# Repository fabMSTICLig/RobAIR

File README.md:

<br />Les différentes partie de ce projet sont mise à disposition selon les termes de la <a rel="license" href="http://creativecommons.org/licenses/by-nc-sa/3.0/fr/">Licence Creative Commons Attribution - Pas d’Utilisation Commerciale - Partage dans les Mêmes Conditions 3.0 France</a>.

---

Avec le soutien financier de 

---

# RobAIR

## Installation

### Pré-requis

- Ubuntu 20.04 LTS
- Git

- L'utilisateur courant doit avoir les droits root via `sudo`

### Procédure

- Téléchargez le dépôt
```bash
git clone https://github.com/FabmsticLig/RobAIR.git
```
- Lancez le script d'installation
```bash
cd RobAIR
./scripts/install.bash
```
- Si l'utilisateur courant n'était préalablement pas dans le groupe `dialout`
(autrement dit, si le script d'installation a affiché "donne à l'utilisateur
l'accès aux ports série"), redémarrez votre session
- Avec la carte Arduino branchée, lancez le chargement des programmes
```bash
robair reload
```

Le script d'installation récupérera des dépôts les paquets nécessaires et
effectuera la configuration initiale de RobAIR. Quelques variables seront aussi
ajoutées au bashrc de l'utilisateur, en plus d'un service systemd permettant de
démarrer et arrêter les programmes.

## Utilisation

### Procédure

Sur RobAIR
- Allumez le robot
- Allumez la tablette
- Branchez la tablette
- Connectez vous au réseau wifi. Si votre RobAIR dispose d'une carte wifi
externe pensez à déconnecter la carte wifi interne (INTEL).
- Ouvrez un terminal et lancez la commande `robair ip`, notez l'adresse IP indiquée (ROBAIR_IP)
- Lancez la commande `robair start`
- Ouvrez chromium et allez à l'adresse https://ROBAIR_IP:6080 (en remplaçant
ROBAIR_IP par l'adresse notée précédemment)

Sur la machine utilisateur
- Allez à l'adresse http://ROBAIR_IP:6081
- Récupérez l'autorité de certification et installez-la sur le navigateur client
- Allez à l'adresse https://ROBAIR_IP:6080

### Gestion

La partie logicielle de RobAIR peut être contrôlée depuis la tablette via le
programme `robair`. Utilisez les commandes suivantes pour respectivement lancer,
arrêter ou redémarrer le logiciel.
```bash
robair start
robair stop
robair restart
```

Si `systemd` est installé (par défaut sous Ubuntu), ces commandes pilotent
RobAIR via un service systemd en session utilisateur. L'intérêt est
essentiellement de permettre le lancement de RobAIR au démarrage, puis de gérer
automatiquement les erreurs (`systemd` relancera le logiciel s'il venait à
planter). Avec quelques modifications il serait aussi possible de
configurer l'activation par socket.

Le programme `robair` permet aussi la mise à jour du logiciel via cette commande
```bash
$ robair update
```
Cela récupérera la dernière version de RobAIR via Git, recompilera les
programmes et mettra à jour la carte Arduino.

## Développement

RobAIR est développé au-dessus de l'architecture [ROS][1].

L'essentiel du code du robot se trouve dans `arduino/libraries`, avec le point
d'entrée dans `arduino/robairarduino`.

L'interface est servie par un serveur `nodejs` résidant dans `interface`.

Si vous souhaitez tester des modifications locales, vous pouvez recompiler les
programmes et recharger la carte Arduino via cette commande
```bash
robair reload
```

 [1]: http://www.ros.org/

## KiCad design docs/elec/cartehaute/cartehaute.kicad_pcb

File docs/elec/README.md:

#Fichiers mécaniques

Le fichier global.xml s'ouvre avec l'utilitaire umlet ou la version en ligne umletino.

##Kicad

Les schémas électroniques sont conçus avec le logiciel open source Kicad.

| Fichiers/dossiers         | Explication                                             |
|---------------------------|---------------------------------------------------------|
| robair.lib                | librairie kicad des composants du projet                |
| robair.pretty             | librairie d'empreinte kicad des composants du projet    | 
| alim5v                    | le projet de la carte d'alimnetation                    | 
| cartehaute                | le projet de la carte de connexion placé dans le buste  |

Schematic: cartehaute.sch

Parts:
P1: D1; Pin_Header_Straight_1x03_Pitch2.54mm
P2: D2; Pin_Header_Straight_1x03_Pitch2.54mm
P3: D3; Pin_Header_Straight_1x03_Pitch2.54mm
P4: D4; Pin_Header_Straight_1x03_Pitch2.54mm
P5: D5; Pin_Header_Straight_1x03_Pitch2.54mm
P6, P8: CONN_01X02; PhoenixContact_MC-G_02x5.08mm_Angled
P7: CONN_01X05; Pin_Header_Straight_1x05_Pitch2.54mm

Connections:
/5V: P1.2, P2.2, P3.2, P4.2, P5.2, P6.2, P8.2
/GND: P1.1, P2.1, P3.1, P4.1, P5.1, P6.1, P8.1
unnamed: P1.3, P7.1
unnamed: P2.3, P7.2
unnamed: P3.3, P7.3
unnamed: P4.3, P7.4
unnamed: P5.3, P7.5

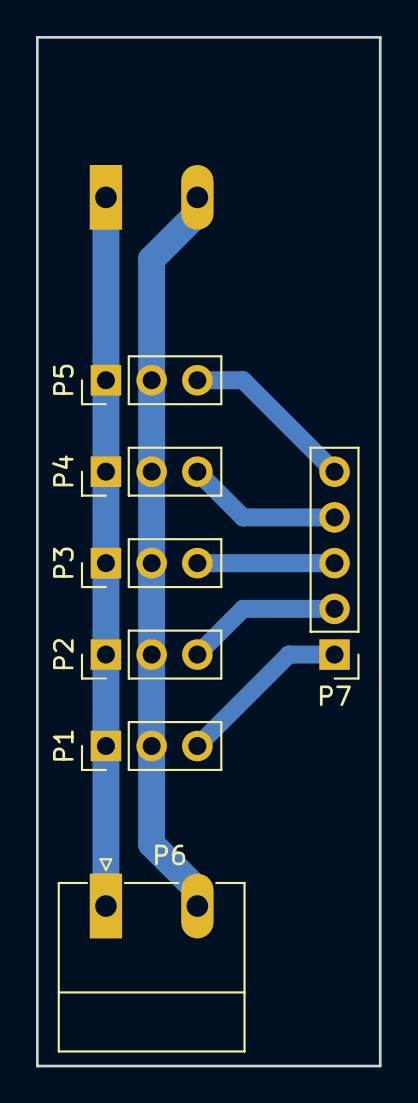
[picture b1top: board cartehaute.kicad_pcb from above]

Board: 2 copper layers, 19.1 x 57.2 mm, 8 parts (1 on the bottom side), 7 nets.

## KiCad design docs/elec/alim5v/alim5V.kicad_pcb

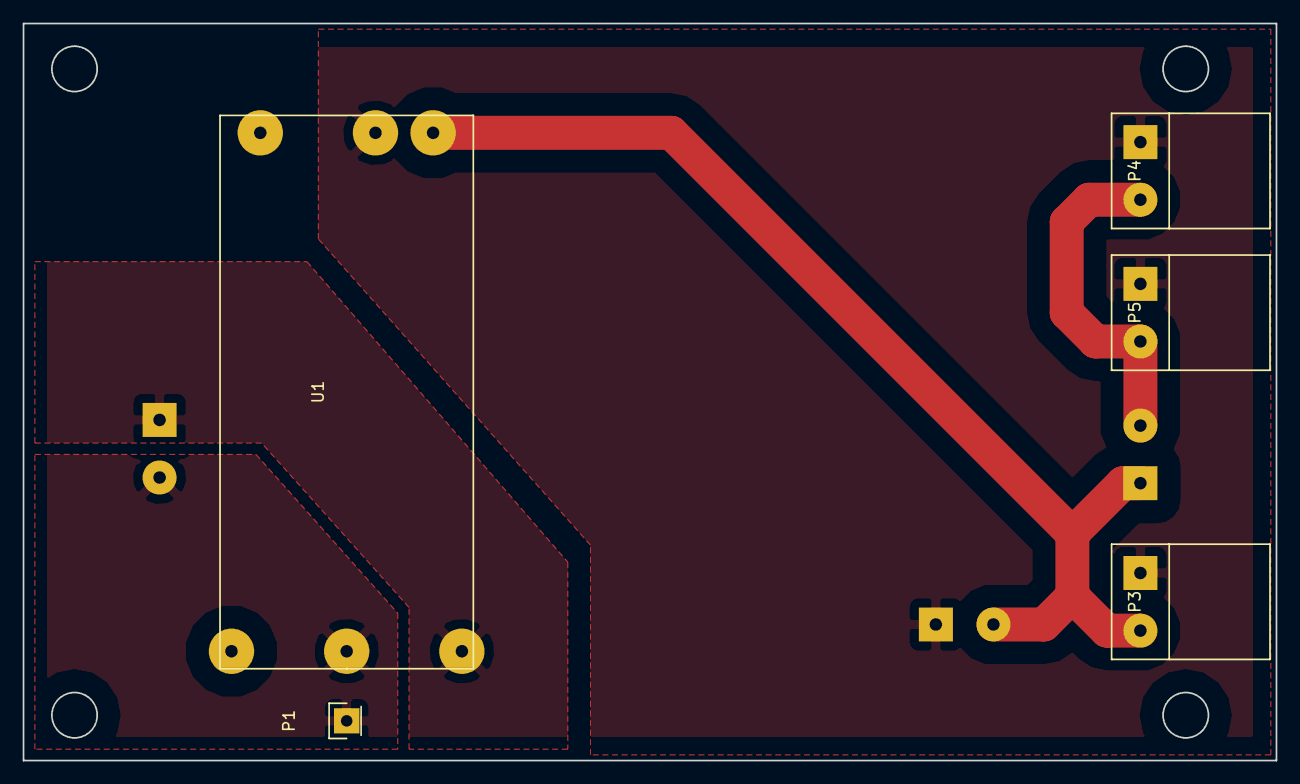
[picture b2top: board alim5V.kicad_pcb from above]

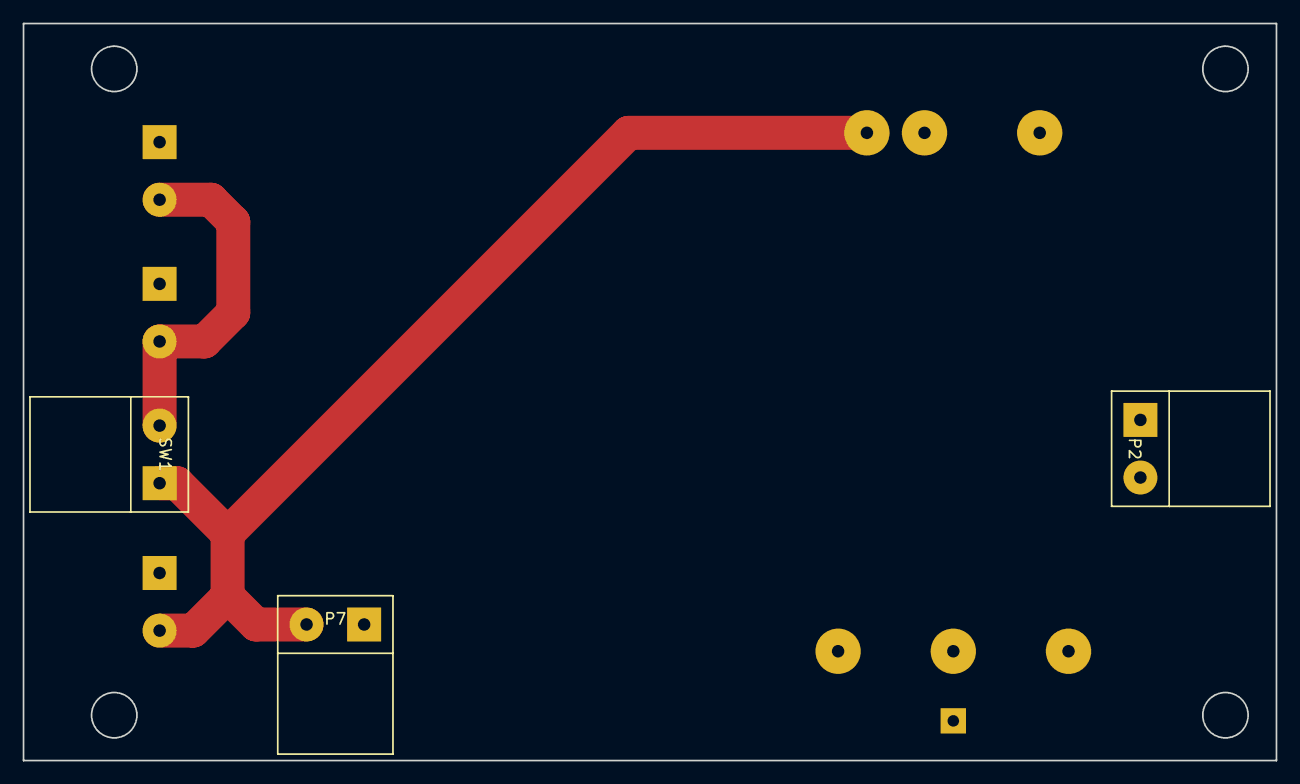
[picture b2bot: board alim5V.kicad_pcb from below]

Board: 2 copper layers, 110.5 x 65.0 mm, 8 parts (3 on the bottom side), 5 nets.

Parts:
P1: GND Ardui; Pin_Header_Straight_1x01
P2: 5V out; Bornier5mm
P3: MD49; Bornier5mm
P4: Charg; Bornier5mm
P5: Batt; Bornier5mm
P7: AUX; Bornier5mm
SW1: SW; Bornier5mm
U1: UEI30-050-Q12P-C

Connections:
/GND5: P1.1, P2.2, U1.5
/GND24: P3.1, P4.1, P5.1, P7.1, U1.2
unnamed: P2.1, U1.4
unnamed: P3.2, P7.2, SW1.1, U1.1
unnamed: P4.2, P5.2, SW1.2

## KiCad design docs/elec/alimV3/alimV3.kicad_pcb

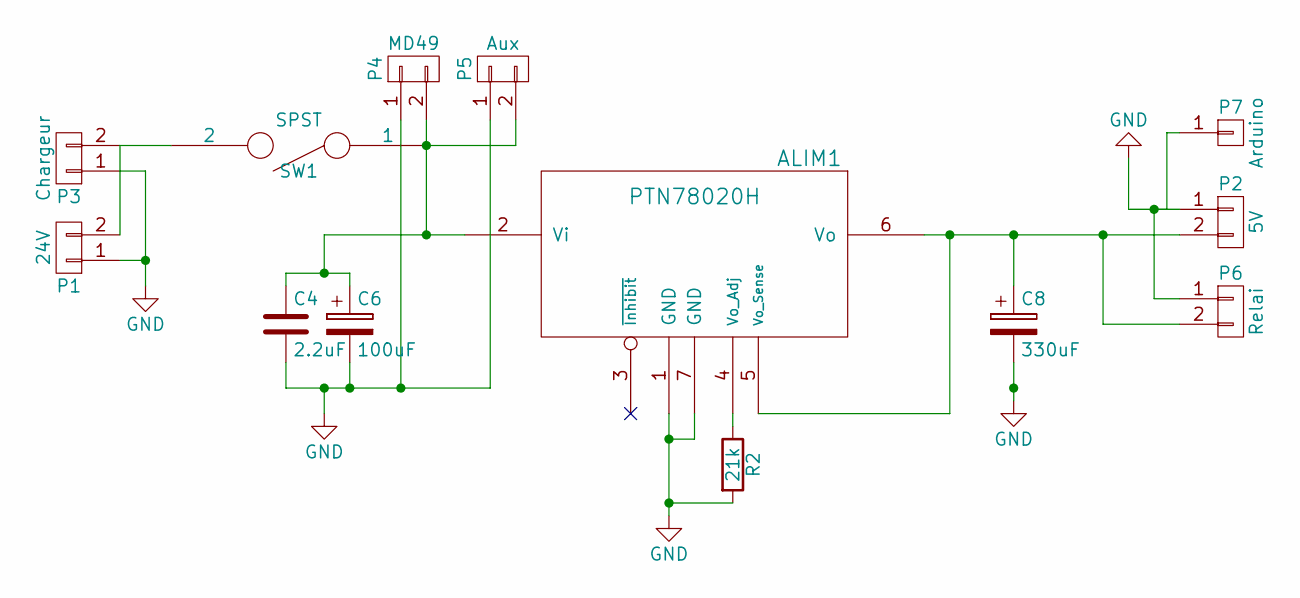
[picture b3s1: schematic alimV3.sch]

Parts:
ALIM1: PTN78020H; PTN78020
C4: 2.2uF; C_1210_HandSoldering
C6: 100uF; CP_Radial_D6.3mm_P2.50mm
C8: 330uF; CP_Radial_D10.0mm_P5.00mm
P1: 24V; Bornier5mm
P2: 5V; Bornier5mm
P3: Chargeur; Bornier5mm
P4: MD49; Bornier5mm
P5: Aux; Bornier5mm
P6: Relai; Socket_Strip_Straight_2x01_Pitch2.54mm
P7: Arduino; Socket_Strip_Straight_1x01_Pitch2.54mm
R2: 21k; R_Axial_DIN0204_L3.6mm_D1.6mm_P2.54mm_Vertical
SW1: SPST; Bornier5mm

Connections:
GND: ALIM1.1 (GND), ALIM1.7 (GND), C4.2, C6.2, C8.2, P1.1, P2.1, P3.1, P4.1, P5.1, P6.1, P7.1, R2.2; also elsewhere on the board
unnamed 1: ALIM1.2 (Vi), C4.1, C6.1, P4.2, P5.2, SW1.1; also elsewhere on the board
unnamed 3: ALIM1.4 (Vo_Adj), R2.1; also elsewhere on the board
unnamed 4: ALIM1.5 (Vo_Sense), ALIM1.6 (Vo), C8.1, P2.2, P6.2; also elsewhere on the board
unnamed: P1.2, P3.2, SW1.2

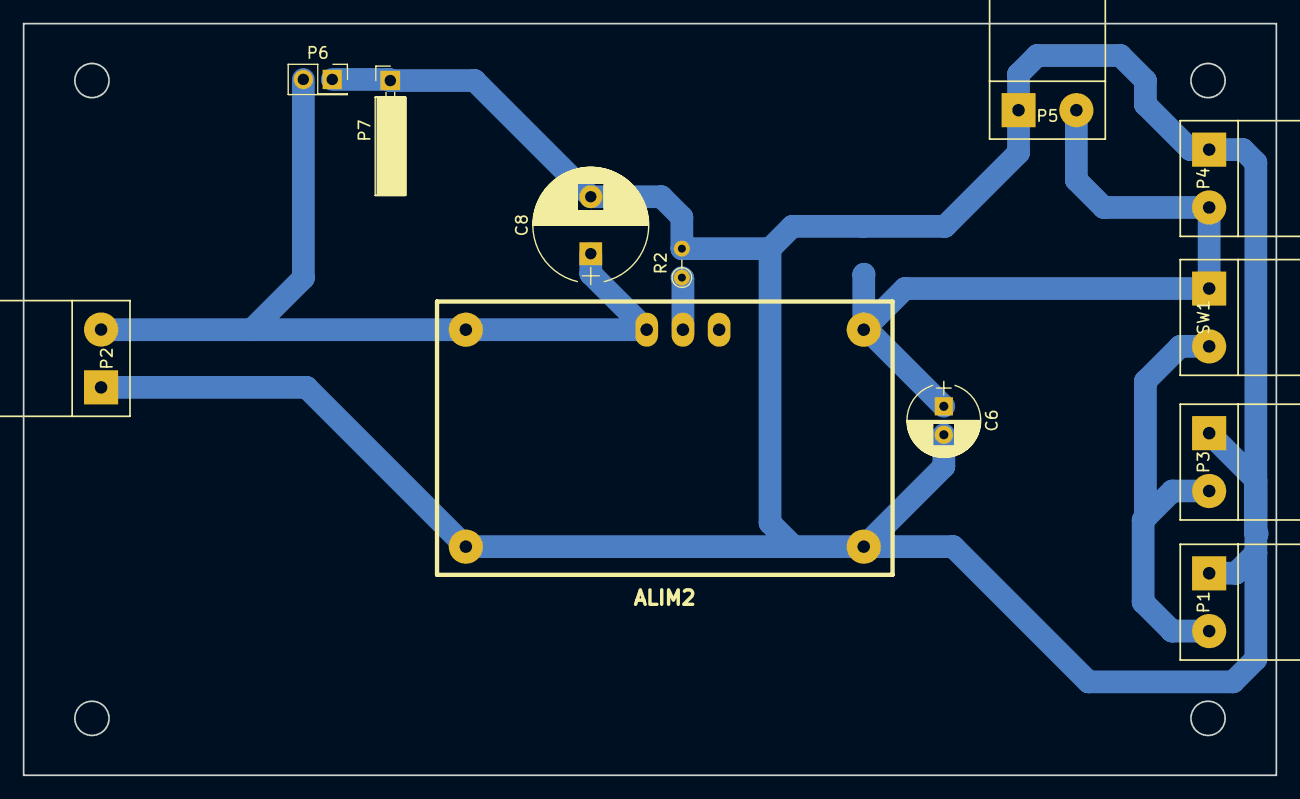
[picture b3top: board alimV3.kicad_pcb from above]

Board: 2 copper layers, 110.0 x 66.0 mm, 13 parts (1 on the bottom side), 5 nets.

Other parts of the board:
ALIM2: PTN78020H; PTN78020

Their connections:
GND: ALIM2.1, ALIM2.7; also elsewhere on the board
unnamed 1: ALIM2.2; also elsewhere on the board
unnamed 3: ALIM2.4; also elsewhere on the board
unnamed 4: ALIM2.5, ALIM2.6; also elsewhere on the board

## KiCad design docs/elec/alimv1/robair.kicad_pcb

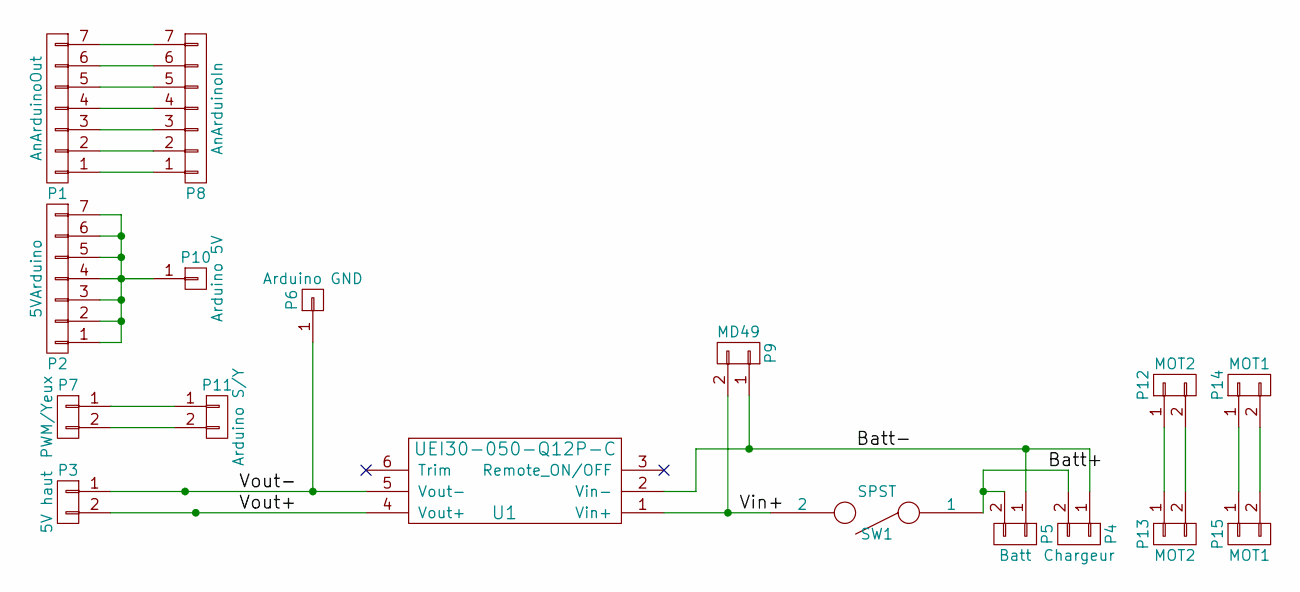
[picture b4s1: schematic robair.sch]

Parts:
P1: AnArduinoOut; Pin_Header_Straight_1x07
P2: 5VArduino; Pin_Header_Straight_1x07
P3: 5V haut; Bornier5mm
P4: Chargeur; Bornier5mm
P5: Batt; Bornier5mm
P6: Arduino GND; Pin_Header_Straight_1x01
P7: PWM/Yeux; Pin_Header_Straight_1x02
P8: AnArduinoIn; Pin_Header_Straight_1x07
P9: MD49; Bornier5mm
P10: Arduino 5V; Pin_Header_Straight_1x01
P11: Arduino S/Y; Pin_Header_Straight_1x02
P12: MOT2; BornierMoteur
P13: MOT2; Bornier5mm
P14: MOT1; BornierMoteur
P15: MOT1; Bornier5mm
SW1: SPST; Bornier5mm
U1: UEI30-050-Q12P-C

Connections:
/Batt+: P4.2, P5.2, SW1.1
/Batt-: P4.1, P5.1, P9.1, U1.2 (Vin-)
/Vin+: P9.2, SW1.2, U1.1 (Vin+)
/Vout+: P3.2, U1.4 (Vout+)
/Vout-: P3.1, P6.1, U1.5 (Vout-)
unnamed: P1.1, P8.1
unnamed: P1.2, P8.2
unnamed: P1.3, P8.3
unnamed: P1.4, P8.4
unnamed: P1.5, P8.5
unnamed: P1.6, P8.6
unnamed: P1.7, P8.7
unnamed: P2.1, P2.2, P2.3, P2.4, P2.5, P2.6, P2.7, P10.1
unnamed: P7.1, P11.1
unnamed: P7.2, P11.2
unnamed: P12.1, P13.1
unnamed: P12.2, P13.2
unnamed: P14.1, P15.1
unnamed: P14.2, P15.2

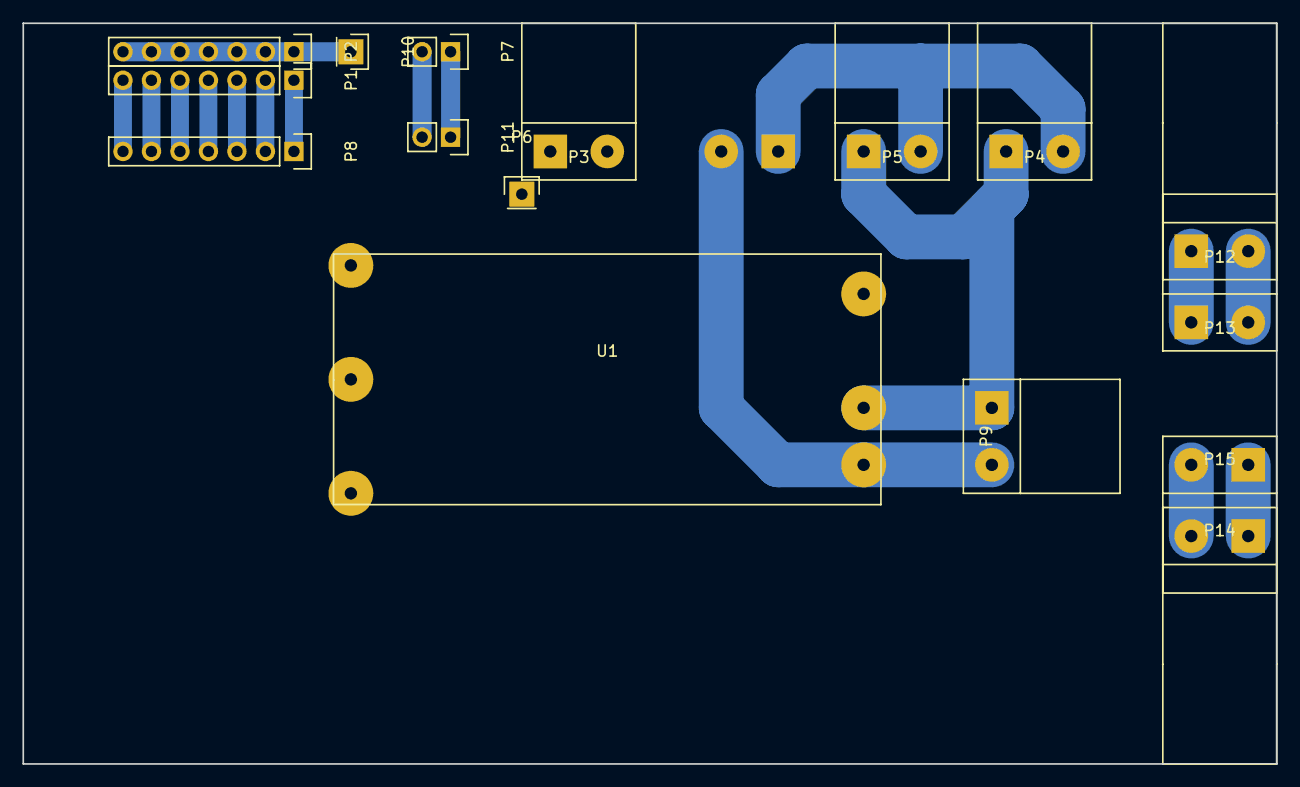
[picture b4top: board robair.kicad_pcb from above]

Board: 2 copper layers, 111.8 x 66.0 mm, 17 parts (1 on the bottom side), 19 nets.

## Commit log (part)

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2016-09-20 création des scripts d'installasion
2016-09-20 Update README.md
    Inline bash style
2016-09-23 correction install.sh
2016-09-26 correction install derrière proxy
2016-10-07 interface glyphicons fonts et jqerry libs
2016-10-07 ajout projet arduino et librairies
2016-10-17 interface jquery
2016-10-18 changement de ports et avancer webinterface
2016-10-20 ajout dossier doc
2016-10-21 fix bug st
2016-10-26 ajout des yeux et rotation tête
2016-10-28 kicad project
2016-11-06 Corrige le bug du proxy https dans install.bash
2016-11-12 fix install.bash
    option -e enlevée, l'option non compatible avec `cat ~/.bashrc | grep ROBAIR`, supposément l'utilisation des ``
2016-11-12 ajout pont scratch
2016-11-20 elec : alim haut, alim bas. mecas
2016-11-24 ros ajout de rosparam dans ros arduino, gestion des bumper (en cours), gestion de l'aru
2016-11-27 correction de la résoltion de ROBAIR_IP en cas de connection offline
2016-11-27 ajout du touché
2016-11-28 ajout script de démarage correction de la gestion des yeux bumper ok touch ok
2016-11-28 ajout des params touchXTresh
2016-11-29 changement param touch
2016-11-29 changement system start & stop & restart
2016-11-29 gestion de la fermeture de la fenetre de controle
2016-12-01 netoyage des fichiers meca, création de la base de charge
2016-12-06 meca ajout support cartes
2016-12-06 ajout carte alim 5V
2016-12-08 Ajout de l'option pour mettre à jour RoAIR
2016-12-08 ajout du changement de bookmark chromium
2016-12-09 Readme ortho
2016-12-09 ajout sketch test Analog
2016-12-25 ajout fichiers decoupes laser
2016-12-25 ajout connecteur carte puissance
2017-01-03 update svg elec
2017-01-16 correction robair home+ scratch
2017-01-16 gestion de la résolution caméra 640x480
2017-01-16 ajout d'un script permettant de modifier les fichiers de configurations selon le ROBAIR_HOME, sortie des fichiers impactés du git et ajout des fichiers par defaut
2017-01-25 robair script: transfert du changement d'ip et d'arduino dans le script robair
2017-02-02 pad mod
2017-02-04 maj de README, "-" enlevé du nom du dossier
2017-02-27 Crée le répertoire catkin_ws/src/robairmain/launch s'il n'existe pas
2017-02-27 Lance changehome.bash à l'installation
2017-02-28 Supprime des fichiers obsolètes
2017-03-01 Corrige MD49::getEncoders
2017-03-07 maj meca
2017-03-07 Récupère signalmaster via un sous-module plutôt que par le script
2017-03-12 typo Readme
2017-03-21 Ne publie plus d'information de statut depuis roswifibot
2017-03-21 Corrige la gestion du timeout dans MD49::getInt
2017-03-21 Lance le noeud d'odométrie avec ses paramètres en même temps que robair
2017-03-21 Supprime les fichiers non relatifs à l'odométrie
2017-03-21 N'écoute plus le topic "cmd_vel" dans roswifibot
2017-03-21 Récupère les informations des moteurs dans le "driver" de roswifibot
2017-03-21 Lance wifibot_tf_broadcaster au lancement de RobAir
2017-03-21 Corrige quelques fautes d'orthographe dans le script d'installation
2017-03-22 Utilise ROBAIR_HOME pour les paramètres de rosbridge dans robair.launch
2017-03-23 Gère le déplacement du robot au joystick
2017-03-23 Gère le mouvement de la tête de RobAIR avec le stick de droite
2017-03-23 Corrige l'orientation des yeux à gauche et à droite
2017-03-24 Recentre la tête lorsqu'on presse la gâchette droite de la manette
2017-03-24 Lie quelques "expressions" des yeux aux touches de droite du gamepad
2017-03-29 Fait réagir Robair aux commandes /cmd_vel
2017-03-29 Corrige le nom des frames pour les transforms envoyées
2017-03-29 Spécifie ROS_IP lors du lancement de robair
2017-03-30 gem liv
2017-03-30 Place robair.launch dans son répertoire
    Etant donné que plus aucun script ne modifie robair.launch, on se
    débarrasse du mécanisme de copie. Cela nous permet en particulier de
    mettre à jour le fichier via Git.
2017-03-30 Trouve la carte Arduino lors du robair start
2017-03-31 Utilise des chemins relatifs pour la configuration du serveur interface
    Cela nous permet de nous débarasser du script changehome.sh, et en règle
    générale de toute dépendance au répertoire d'installation
2017-03-31 Ajoute l'emplacement habituel d'avrdude.conf au Makefile Arduino
2017-03-31 Simplifie le script d'installation
2017-03-31 Ajoute une commande reload et réécrit l'update
2017-04-14 Utilise la bibliothèque Adafruit_TiCoServo pour piloter la tête
    Contrairement à la bibiliothèque Servo, celle-ci n'utilise pas
    d'interruptions pour piloter les servomoteurs. A la place, elle tire
    profit des timers 16 bits du microcontrolleur, capables de générer
    automatiquement des impulsions avec la bonne largeur (PWM).
    Cela permet d'utiliser les NeoPixels sans déranger le contrôle du
    servomoteur. En effet, la configuration des LEDs se fait par l'envoi
2017-05-18 Ajoute l'adresse IP en altname pour le certificat x509
    Ceci est requis par Chrome depuis la version 58. Les certificats x509 v1
    avec uniquement un CN (Common Name) ne sont plus supportés. Ce commit
    permet de générer des certificats x509 v3 avec un SAN (Subject
    Alternative Name).
2017-05-30 add dock node called dockmain
2017-05-31 add dock characteristic, add dock node for robair and the robot is now docking in reverse
2017-06-06 add a passive solution for docking
2017-06-06 change passive code and dockmain code
2017-06-07 Ajout d'un lien vers l'installation d'OpenCV
2017-06-07 move 'README.md' for dock, add 'Markers' directoy
2017-06-07 algorithme modification
2017-06-13 enslavement and no misplaced state
2017-06-14 change enslavement
2017-06-21 change state and enslavement
2017-06-21 add calibration images for RaspberryPi camera v2.1
2017-06-21 add swerve mesurement
2017-06-21 untrack deleted files
2017-06-21 new calibration images path
2017-06-21 desindex
2017-06-22 Update dock_passive.py
    Remove error line
2017-06-23 add dock ID
2017-06-23 Stop docking when dock request and not docked
2017-06-26 use marker index
2017-06-26 change move and turn enslavement
2017-06-27 OpenHAB demonstration
2017-06-27 start iot pkg, dock_active and dock_passive with robair start
2017-06-28 Crée un service systemd pour RobAIR
2017-06-28 Embellit l'affichage des commandes ip et start quand l'IP a changé
2017-06-28 Lance tout de même RobAIR si aucune carte Arduino n'est trouvée
2017-06-28 Ajoute l'utilisateur au groupe dialout lors de l'installation
2017-06-28 Exclut du dépôt les fichiers de back-up de différents éditeurs de texte
2017-06-28 Lance RobAIR avec systemd si robair.service est installé
2017-06-28 Corrige l'affichage quand les scripts sont lancés sans terminal
2017-06-28 Retire le fichier catkin_ws/src/CMakeLists.txt du dépôt
2017-06-28 Détecte la carte Arduino dans `robair reload` pour la passer au Makefile
2017-06-28 Remet en place une commande `robair ip` qui affiche l'adresse IP
2017-06-28 Réécrit le README
2017-06-28 Ne lisse pas le changement de vitesse si la commande est cmdvel
2017-06-30 linear enslavement changed
2017-06-30 new design
2017-07-03 adjustements
2017-07-07 corrections
2017-07-19 Ajoute la bibliothèque vl53l0x-arduino
2017-07-25 Publie les valeurs de distance à chaque tour de boucle
2017-07-26 Attend que la connexion à ROS soit établie pour configurer les capteurs
2017-07-28 Désactive tous les capteurs au démarrage même si non déclarés
2017-09-08 Ne configure les capteurs qu'après publication des topics
    L'attente du paramètre distance-sensors et la configuration des capteurs
    (probablement la première) causait un problème lors de la réception des
    topics du côté de rosserial_python. Les publishers et subscribers
    n'étant pas configurés, la carte Arduino ne pouvait alors plus rien
    envoyer ni recevoir. Déplacer ces actions après la publication des
    publishers et subscribers corrige le problème.
2017-09-27 update elec
2017-10-16 Ajoute un moyen de lancer le simulateur lui-même sous gdb
2017-10-16 Ajoute un patron de code et le Makefile pour le simulateur
2017-10-16 Ajoute une option pour débugguer le programme Arduino
2017-10-16 Ne rafraîchit l'interface que 20 fois par seconde
2017-10-16 Implémente la simulation des servomoteurs
2017-10-16 Implémente une interface graphique pour voir l'angle de la tête
2017-10-16 Définit un servo dans main pour la tête de RobAIR
2017-10-16 Affiche la vitesse actuelle sur l'interface graphique
2017-10-16 Simule une carte MD49
2017-10-16 Ajoute un README
2017-10-16 Effectue un make clean sur le code Arduino lors d'un robair reload
2017-10-16 Remet en place le sous-module pour Adafruit_NeoPixel
2017-10-19 Corrige le bug qui bloquait le simulateur avec Adafruit_TiCoServo
2017-10-19 Installe le paquet ros-kinetic-tf, nécessaire pour odometry
2017-10-20 Ajoute une mailmap pour uniformiser le retour de git shortlog
2017-10-25 Détecte obligatoirement une Arduino Mega
2017-10-27 Corrige la vitesse angulaire demandée par l'interface
2017-10-27 Diminue la vitesse d'accélération du MD49
2017-10-27 Corrige le contrôle au gamepad pour utilser /cmd_vel
2017-10-27 Corrige l'ordre des moteurs pour les commandes SET_SPEED du MD49
2017-10-27 Supprime /cmdmotors
2017-11-02 Ajoute un facteur pour réduire la vitesse angulaire
2017-11-02 Installe mongodb_store
2017-11-02 Récupère les paramètres de la correction fisheye au chargement
2017-11-02 Active le noeud config_manager
2017-11-02 Enregistre les préférences vis-à-vis de la correction de la vidéo
2017-11-03 Nettoie le code Arduino et uniformise le coding style
2017-11-03 Déplace last_ip et last_arduino dans data/
2017-11-23 clean des fichiers méca
2017-11-28 fix la dependence de odometry au messages robairmain
2017-11-28 [robairsim] Corrige le flag de debug dans le README pour utiliser DWARF4
2017-11-29 Utilise une version de rosserial sans timeout par message
2017-11-29 Diminue la vitesse du lien série Arduino <-> tablette à 9600 bauds
    A une vitesse plus élevée, l'Arduino perd des données. En effet, le
    tampon n'est que de 64 octets. Sachant qu'un tour de boucle utilise 50
    millisecondes plus le temps de traitement, une vitesse supérieure à 9600
    bauds (960 octets par seconde, soit 48 par 50 ms) serait trop grande.
2017-11-29 Place les matrices d'yeux constantes en mémoire flash (lecture seule)
2017-11-29 Implémente un moyen d'envoyer un motif quelconque pour les yeux
2017-11-29 Ajoute des fonctions à la bibliothèque Eyes pour gérer des animations
2017-11-30 [robairsim] Supprime le port série virtuel à la fermeture du programme
2017-12-05 ajout carte alimentation générique
2017-12-05 meca : ajustement des trous de la tour électrique
2017-12-13 Installe scons à l'installation de RobAIR (requis par libmongocxx_ros)
2017-12-13 Met à jour rosserial
2018-01-11 Corrige la commande pour obtenir l'IP de la machine
2018-01-19 Met à jour les yeux sur l'interface lors de la réception d'un motif
2018-01-22 Ajoute le logo de la région Auvergne-Rhône-Alpes au README
2018-01-26 Corrige la mise en forme du code de la télécommande côté RobAIR
2018-01-26 Change le protocole de la télécommande pour utiliser un format binaire
2018-03-05 Ne regénère pas ROBAIR_IP si la variable est déjà positionnée
2018-03-14 Rend les boutons opérationnels sur tablette tactile
2018-05-21 docs réajustement du pcb de la carte alim
2018-05-21 docs transfere de deux découpes de la tête vers le buste
2018-06-19 Ajout du diagramme du cablage elec
2018-12-03 Correction des evenements touch
2019-01-14 change la taille de l'affichage des yeux.
2019-01-18 modification de la taille des yeux
2019-06-19 Add hold file for the electronic tower
2019-12-09 Add the model of two hold for the electronical tower
2019-12-09 Complete gitignore for kicad files
2021-10-28 Gestion Alim2021 dans code arduino
2021-11-16 Fix install old kinetic value
2022-03-10 config ip eth
2022-03-29 exit on error
2022-06-21 check if network can be reach to install dependencies
